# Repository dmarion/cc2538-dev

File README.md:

cc2538-dev
==========

Eagle schematics and PCB design files for CC2538 Development Board

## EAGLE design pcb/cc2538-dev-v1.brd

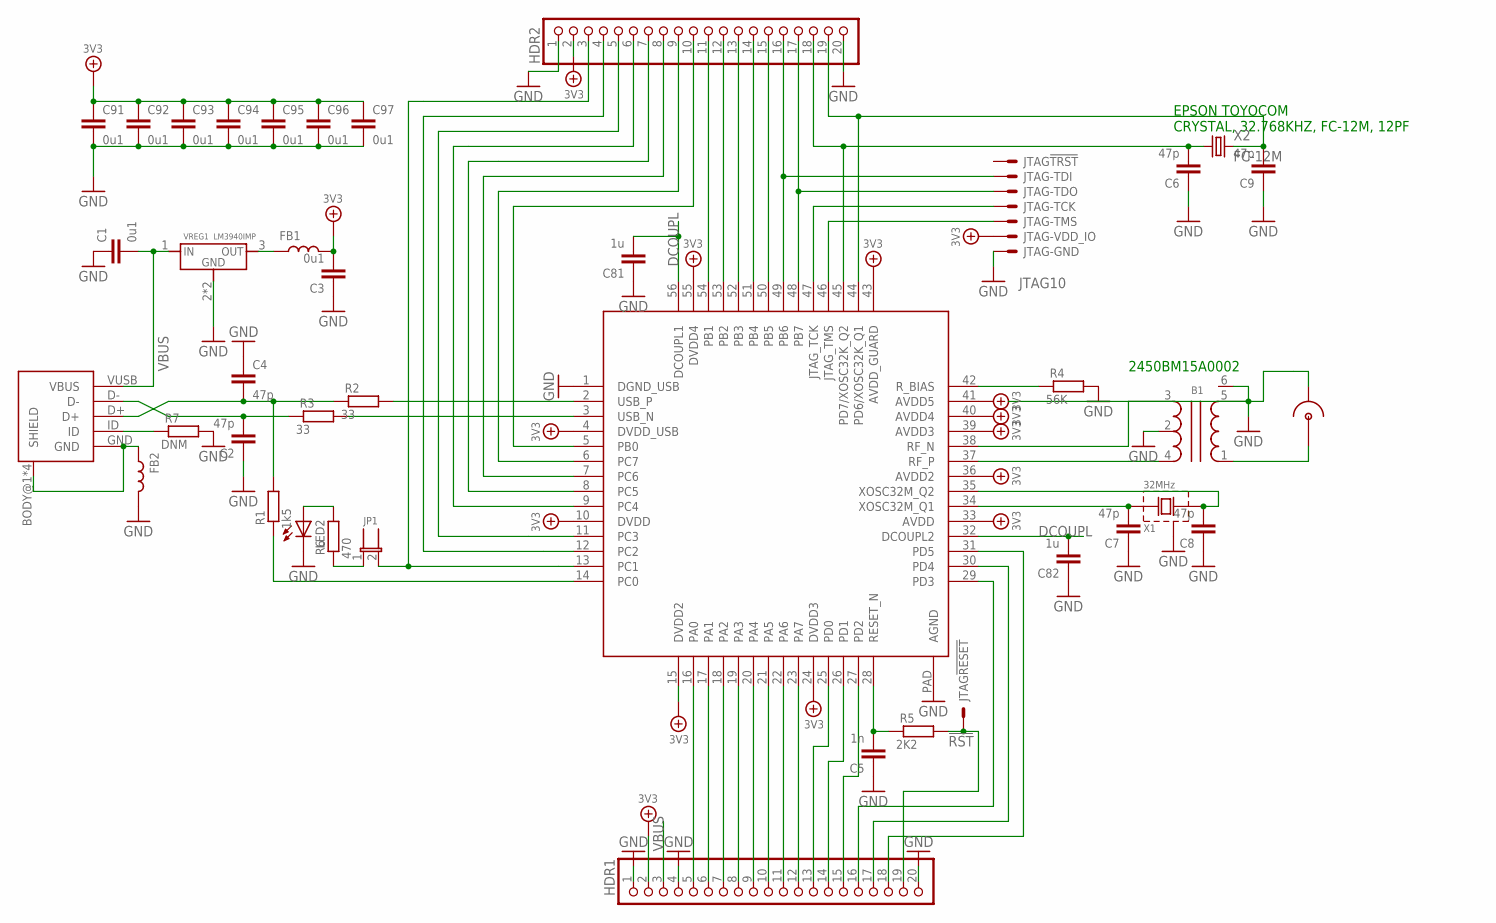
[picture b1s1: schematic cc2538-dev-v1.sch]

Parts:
B1: BALUN; BALUN-0805
C1, C3: 0u1; C1206
C2, C4, C6, C7, C8, C9: 47p; C0603
C5: 1n; C0603
C81, C82: 1u; C0402
C91, C92, C93, C94, C95, C96, C97: 0u1; C0402
CN1: USB-OTG; CONN_USB_MINI-B
CN2: RF-CONNSMA; SMA
FB1, FB2: L0603; R603
HDR1, HDR2: PINHD-1X20; 1X20
JP1: JP-2MM-2
JTAG: JTAG10; HDR-2X5-2.00
LED2: LED805; LED-805
R1: 1k5; R603
R2, R3: 33; R603
R4: 56K; R603
R5: 2K2; R603
R6: 470; R603
R7: DNM; R603
U1: CC2538; QFN56
VREG1: LM3940IMP; SOT223
X1: 32MHz; XTAL-4-3225
X2: FC-12M

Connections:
3V3: C3.2, C91.1, C92.1, C93.1, C94.1, C95.1, C96.1, C97.1, FB1.2, HDR1.2, HDR2.2, JTAG.1, JTAG.2, U1.4 (DVDD_USB), U1.10 (DVDD), U1.15 (DVDD2), U1.24 (DVDD3), U1.33 (AVDD), U1.36 (AVDD2), U1.39 (AVDD3), U1.40 (AVDD4), U1.41 (AVDD5), U1.43 (AVDD_GUARD), U1.55 (DVDD4)
!RST: HDR1.19, JTAG.4, R5.2
!RST_PIN: C5.2, R5.1, U1.28 (RESET_N)
CN1: C4.2, CN1.D+, R1.2, R2.1
DCOUPL: C81.2, C82.2, U1.32 (DCOUPL2), U1.56 (DCOUPL1)
GND: B1.2, B1.5, B1.6, C1.1, C2.1, C3.1, C4.1, C5.1, C6.1, C7.1, C8.1, C9.1, C81.1, C82.1, C91.2, C92.2, C93.2, C94.2, C95.2, C96.2, C97.2, CN2.GND1 (GND), CN2.GND2 (GND), CN2.GND3 (GND), CN2.GND4 (GND), FB2.2, HDR1.1, HDR1.4, HDR1.20, HDR2.1, HDR2.20, JTAG.8, JTAG.10, LED2.C, R4.2, R7.2, U1.1 (DGND_USB), U1.PAD (AGND), VREG1.2 (GND), VREG1.4 (GND), X1.2 (GND1), X1.4 (GND1)
unnamed: R2.2, U1.2 (USB_P)
unnamed: R3.2, U1.3 (USB_N)
unnamed: CN1.BODY@1 (SHIELD), CN1.BODY@2 (SHIELD), CN1.BODY@3 (SHIELD), CN1.BODY@4 (SHIELD), CN1.GND, FB2.1
unnamed: R1.1, U1.14 (PC0)
unnamed: R4.1, U1.42 (R_BIAS)
unnamed: JTAG.9, U1.47 (JTAG_TCK)
unnamed: JTAG.7, U1.46 (JTAG_TMS)
unnamed: HDR1.5, U1.16 (PA0)
unnamed: HDR1.6, U1.17 (PA1)
unnamed: HDR1.7, U1.18 (PA2)
unnamed: HDR1.8, U1.19 (PA3)
unnamed: C2.2, CN1.D-, R3.1
unnamed: HDR1.9, U1.20 (PA4)
unnamed: HDR1.10, U1.21 (PA5)
unnamed: HDR1.11, U1.22 (PA6)
unnamed: HDR1.12, U1.23 (PA7)
unnamed: FB1.1, VREG1.3 (OUT)
unnamed: HDR2.3, JP1.2, U1.13 (PC1)
unnamed: HDR2.4, U1.12 (PC2)
unnamed: HDR2.5, U1.11 (PC3)
unnamed: HDR1.14, U1.26 (PD1)
unnamed: HDR1.13, U1.25 (PD0)
unnamed: C6.2, HDR2.18, U1.45 (PD7/XOSC32K_Q2), X2.1
unnamed: HDR1.16, U1.29 (PD3)
unnamed: HDR1.17, U1.30 (PD4)
unnamed: HDR1.18, U1.31 (PD5)
unnamed: B1.3, U1.38 (RF_N)
unnamed: B1.4, U1.37 (RF_P)
unnamed: C8.2, U1.35 (XOSC32M_Q2), X1.3 (X2)
unnamed: C7.2, U1.34 (XOSC32M_Q1), X1.1 (X1)
unnamed: HDR2.15, U1.50 (PB5)
unnamed: HDR1.15, U1.27 (PD2)
unnamed: HDR2.10, U1.5 (PB0)
unnamed: HDR2.9, U1.6 (PC7)
unnamed: HDR2.8, U1.7 (PC6)
unnamed: HDR2.7, U1.8 (PC5)
unnamed: HDR2.12, U1.53 (PB2)
unnamed: HDR2.11, U1.54 (PB1)
unnamed: C9.2, HDR2.19, U1.44 (PD6/XOSC32K_Q1), X2.2
unnamed: HDR2.14, U1.51 (PB4)
unnamed: HDR2.6, U1.9 (PC4)
unnamed: HDR2.13, U1.52 (PB3)
unnamed: JP1.1, R6.1
unnamed: LED2.A, R6.2
unnamed: CN1.ID, R7.1
PB6: HDR2.16, JTAG.5, U1.49 (PB6)
PB7: HDR2.17, JTAG.6, U1.48 (PB7)
RF: B1.1, CN2.SIG (SIGNAL)
VBUS: C1.2, CN1.VUSB (VBUS), HDR1.3, VREG1.1 (IN)

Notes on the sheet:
EPSON TOYOCOM CRYSTAL, 32.768KHZ, FC-12M, 12PF
2450BM15A0002

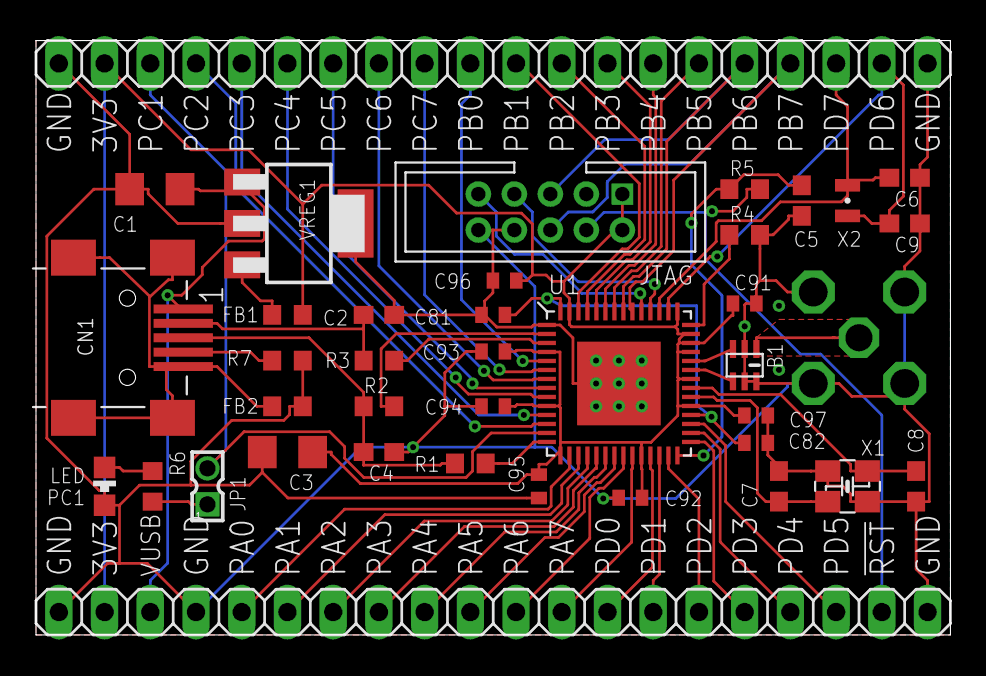
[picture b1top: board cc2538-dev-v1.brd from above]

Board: 2 copper layers, 50.8 x 33.0 mm, 39 parts (0 on the bottom side), 55 nets.

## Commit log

2013-11-16 Add schematics and board PDFs

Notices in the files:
pcb/cc2538-dev-v1.brd:
(c) 2013, Damjan Marion
